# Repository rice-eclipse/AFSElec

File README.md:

This is the official GitHub Repo for Rice ECLIPSE AFS.

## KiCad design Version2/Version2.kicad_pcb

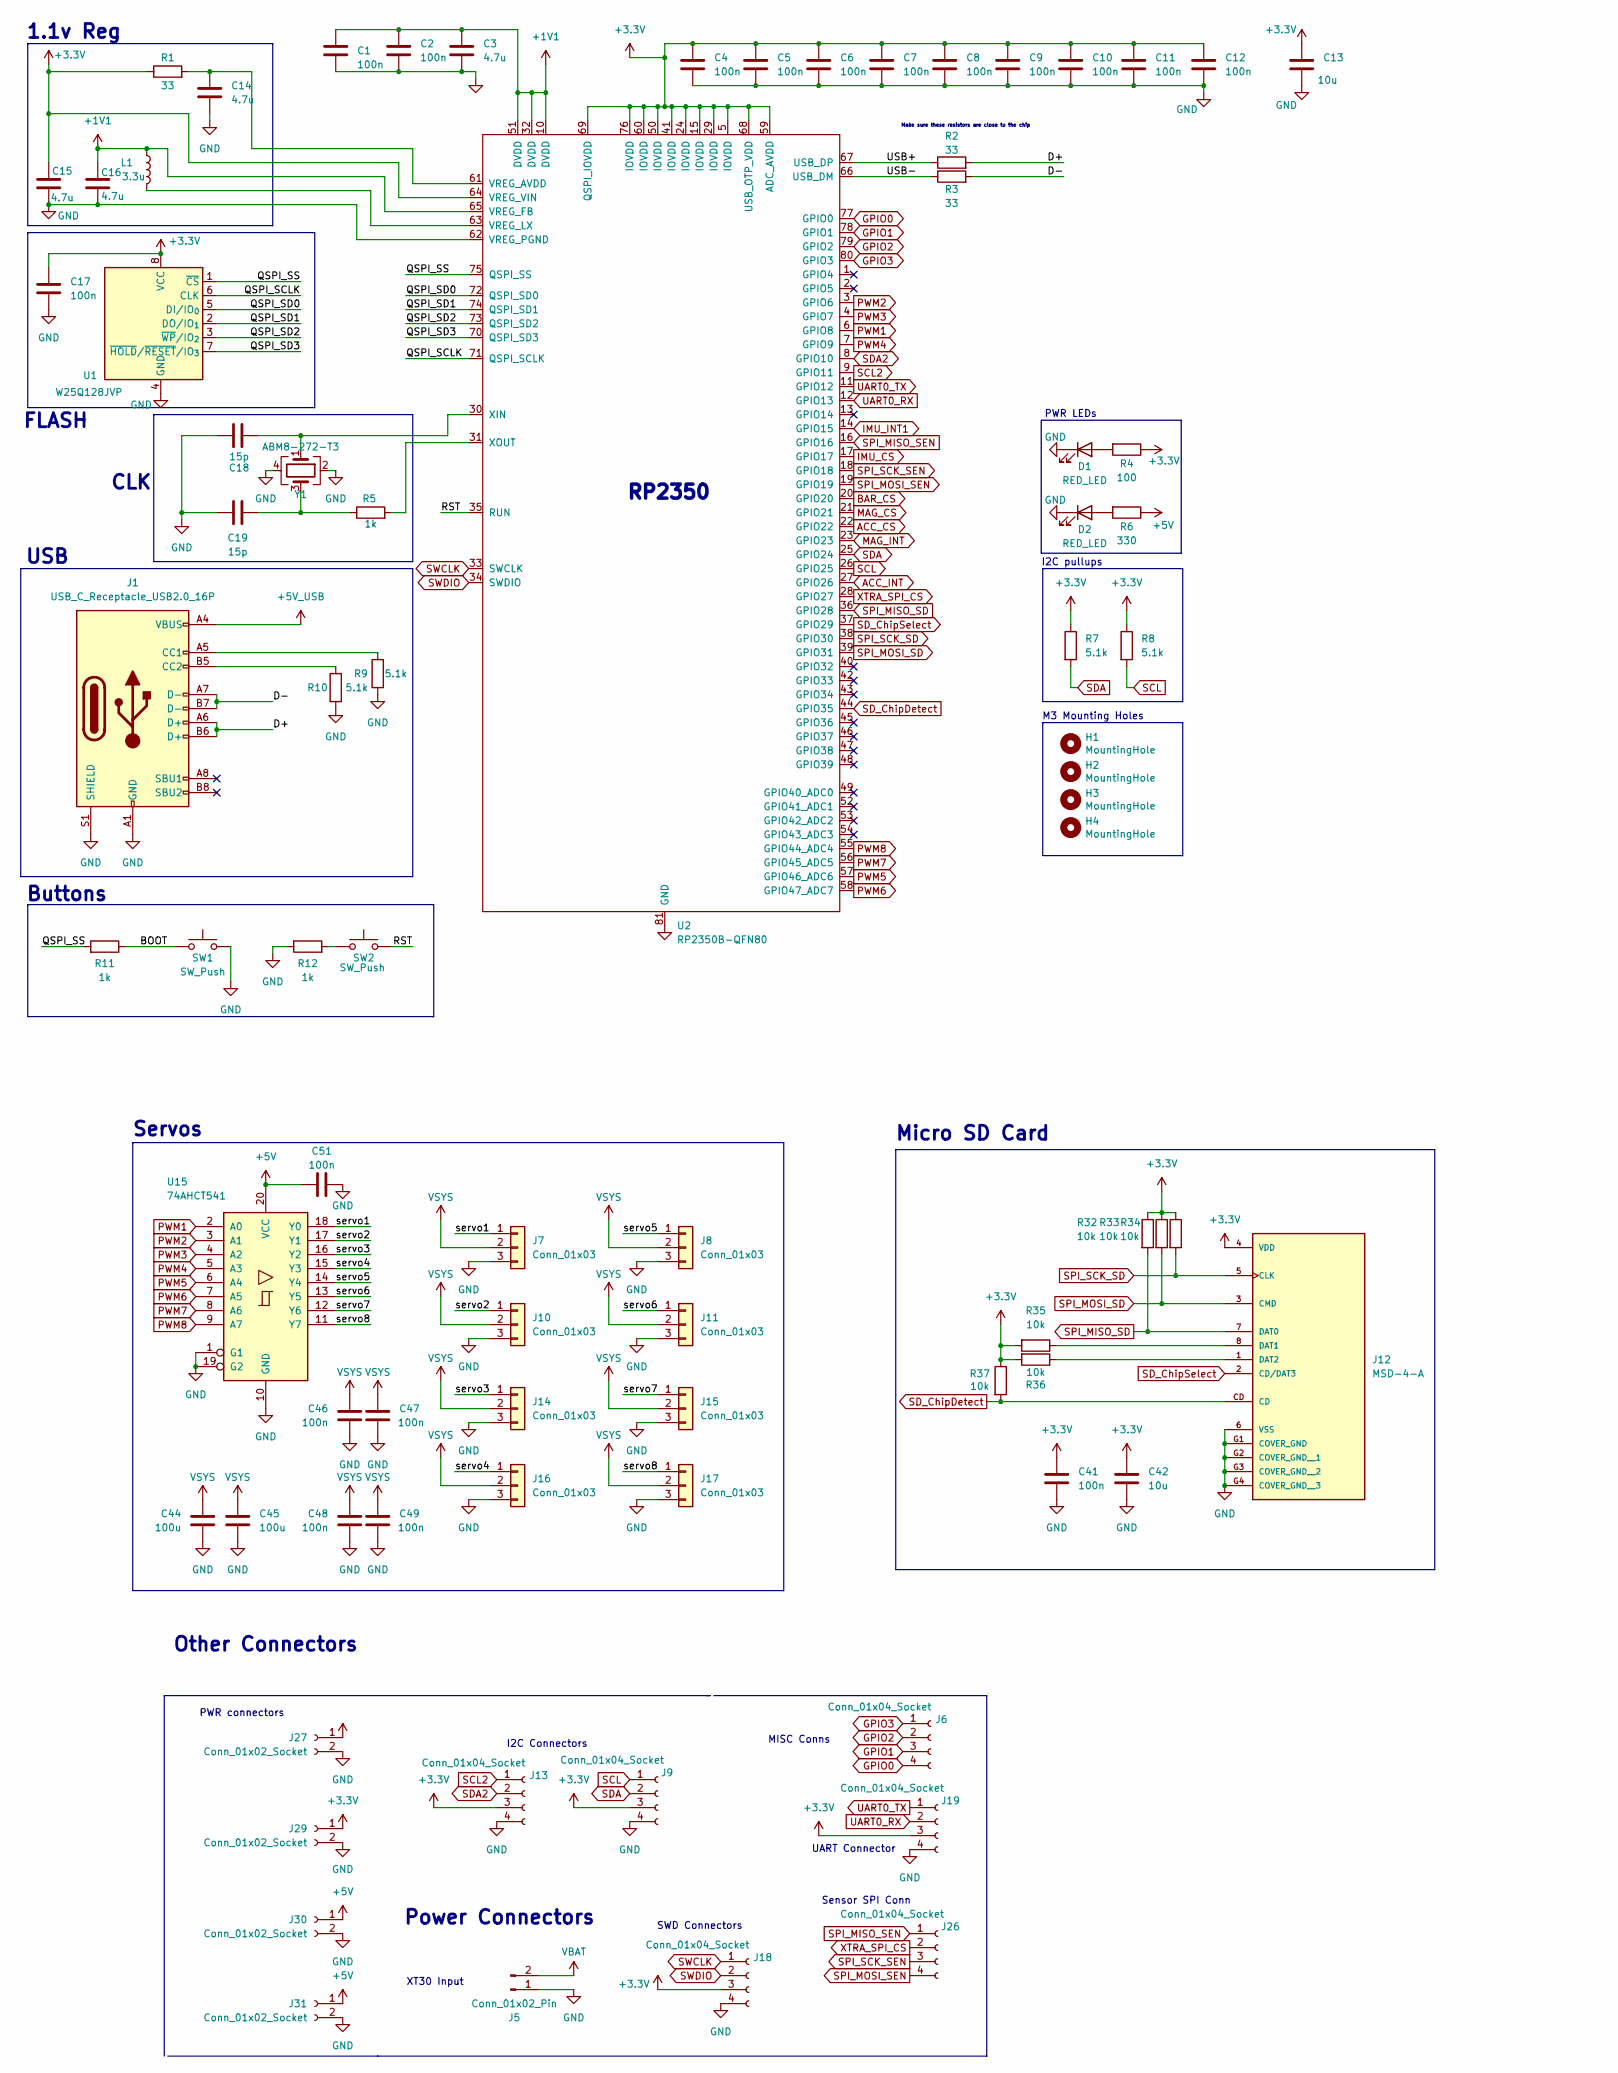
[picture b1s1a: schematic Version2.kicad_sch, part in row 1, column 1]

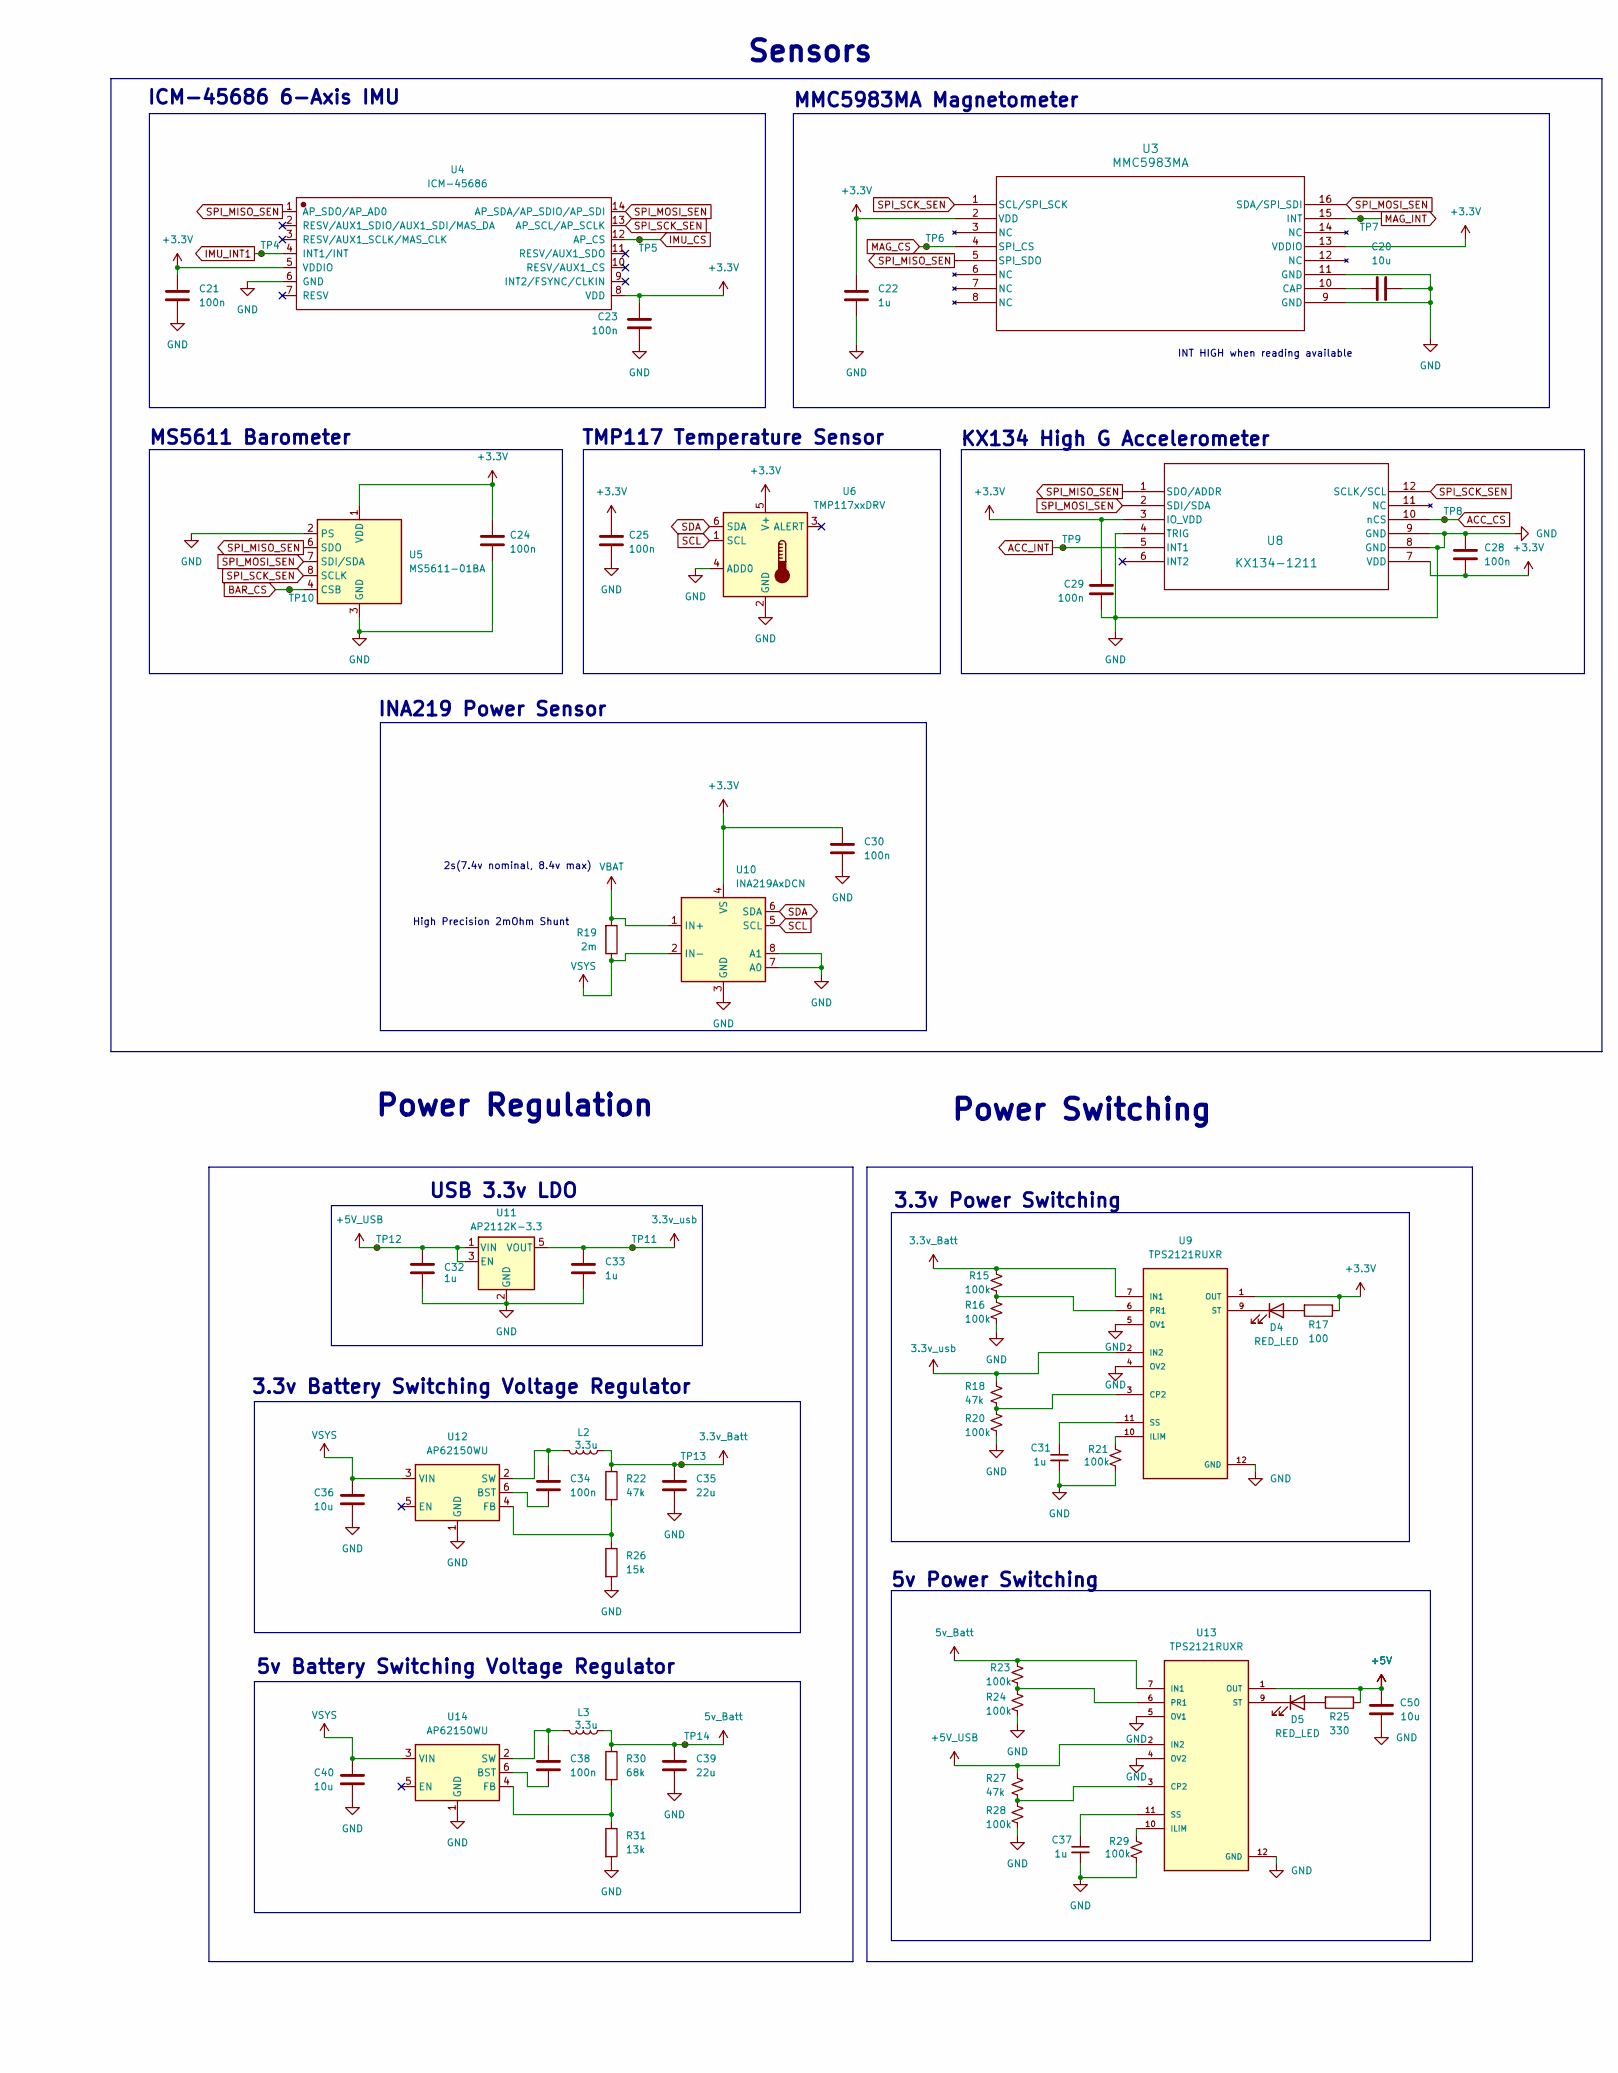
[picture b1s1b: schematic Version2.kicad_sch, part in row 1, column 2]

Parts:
C1, C2, C4, C5, C6, C7, C8, C9, C10, C11, C12, C17, C21, C23, C24, C25, C28, C29, C30, C34, C38, C41, C46, C47, C48, C49, C51: 100n; C_0603_1608Metric; LCSC Part Number C14663
C3, C14, C15, C16: 4.7u; C_0805_2012Metric; LCSC Part Number C1779
C13, C20, C42: 10u; C_0805_2012Metric; LCSC Part Number C15850
C18, C19: 15p; C_0603_1608Metric; LCSC Part Number C1644
C22, C31, C32, C33, C37: 1u; C_0805_2012Metric; LCSC Part Number C28323
C35, C39: 22u; C_0805_2012Metric; LCSC Part Number C45783
C36, C40, C50: 10u; C_0805_2012Metric; JLCPCB Part # C15850
C44, C45: 100u; C_Radial_D5.0mm_H11.0mm_P2.00mm
D1, D2, D4, D5: RED_LED; LED_0805_2012Metric; LCSC Part Number C84256
H1, H2, H3, H4: MountingHole; MountingHole_3.2mm_M3_ISO14580_Pad
J1: USB_C_Receptacle_USB2.0_16P; USB_C_Receptacle_HRO_TYPE-C-31-M-12
J5: Conn_01x02_Pin; AMASS_XT30PW-M_1x02_P2.50mm_Horizontal
J6, J9, J13, J18, J19, J26: Conn_01x04_Socket; JST_PH_B4B-PH-K_1x04_P2.00mm_Vertical
J7, J8, J10, J11, J14, J15, J16, J17: Conn_01x03; PinHeader_1x03_P2.54mm_Vertical
J12: MSD-4-A; CUI_MSD-4-A; PARTREV 1.0; LCSC Part Number C22367949
J27, J29, J30, J31: Conn_01x02_Socket; JST_PH_B2B-PH-K_1x02_P2.00mm_Vertical
L1, L2, L3: 3.3u; AOTA-B201610S3R3-101-T(L_0806_2016metric); LCSC Part Number C42411119
R1, R2, R3: 33; R_0603_1608Metric; LCSC Part Number C23140
R4, R17: 100; R_0603_1608Metric; LCSC Part Number C22775
R5, R11, R12: 1k; R_0603_1608Metric; LCSC Part Number C21190
R6, R25: 330; R_0603_1608Metric; LCSC Part Number C23138
R7, R8, R9, R10: 5.1k; R_0603_1608Metric; LCSC Part Number C23186
R15, R16, R20, R21, R23, R24, R28, R29: 100k; R_0603_1608Metric; LCSC Part Number C25803
R18, R22, R27: 47k; R_0603_1608Metric; LCSC Part Number C25819
R19: 2m; R_1206_3216Metric
R26: 15k; R_0603_1608Metric; LCSC Part Number C22809
R30: 68k; R_0603_1608Metric; LCSC Part Number C23231
R31: 13k; R_0603_1608Metric; LCSC Part Number C22797
R32, R33, R34, R35, R36, R37: 10k; R_0603_1608Metric; LCSC Part Number C25804
SW1, SW2: SW_Push; SW_Push_SPST_NO_Alps_SKRK; LCSC Part Number C115357
TP4, TP5, TP6, TP7, TP8, TP9, TP10, TP11, TP12, TP13, TP14: TestPoint_Small; TestPoint_Pad_1.0x1.0mm
U1: W25Q128JVP; WSON-8-1EP_6x5mm_P1.27mm_EP3.4x4mm; LCSC Part Number C190862
U2: RP2350B-QFN80; QFN-80-1EP_10x10mm_P0.4mm_EP3.4x3.4mm; LCSC Part Number C42415655
U3: MMC5983MA; LGA-16_3x3mm_P0.5mm; LCSC Part Number C404329
U4: ICM-45686; Bosch_LGA-14_3x2.5mm_P0.5mm; Manufacturer Part ICM-45686; LCSC C22459454
U5: MS5611-01BA; LGA-8_3x5mm_P1.25mm; LCSC Part Number C15639
U6: TMP117xxDRV; WSON-6-1EP_2x2mm_P0.65mm_EP1x1.6mm; LCSC Part Number C699536
U8: KX134-1211; LGA-12_2x2mm_P0.5mm; LCSC Part Number C2157908
U9, U13: TPS2121RUXR; Texas_VQFN-HR-12_2x2.5mm_P0.5mm; LCSC Part Number C485916
U10: INA219AxDCN; SOT-23-8; LCSC Part Number SOT-23-8
U11: AP2112K-3.3; SOT-23-5; LCSC Part Number C23380830
U12, U14: AP62150WU; TSOT-23-6; LCSC Part Number C3194237
U15: 74AHCT541; SSOP-20_4.4x6.5mm_P0.65mm; LCSC Part Number C2675635
Y1: ABM8-272-T3; Crystal_SMD_3225-4Pin_3.2x2.5mm; LCSC Part Number C20625731

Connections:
3.3v_Batt: C35.1, L2.1, R15.1, R22.1, TP13.1, U9.7 (IN1)
3.3v_usb: C33.1, R18.1, TP11.1, U9.2 (IN2), U11.5 (VOUT)
5v_Batt: C39.1, L3.1, R23.1, R30.1, TP14.1, U13.7 (IN1)
+1V1: C1.1, C2.1, C3.1, C16.1, L1.1, U2.10 (DVDD), U2.32 (DVDD), U2.51 (DVDD), U2.65 (VREG_FB)
+3.3V: C4.1, C5.1, C6.1, C7.1, C8.1, C9.1, C10.1, C11.1, C12.1, C13.1, C15.1, C17.1, C21.1, C22.2, C23.1, C24.1, C25.1, C28.2, C29.1, C30.1, C41.1, C42.1, J9.3, J12.4 (VDD), J13.3, J18.3, J19.3, J27.1, J29.1, R1.1, R4.1, R7.1, R8.1, R17.1, R32.1, R33.1, R34.1, R35.2, R36.2, R37.1, U1.8 (VCC), U2.5 (IOVDD), U2.15 (IOVDD), U2.24 (IOVDD), U2.29 (IOVDD), U2.41 (IOVDD), U2.50 (IOVDD), U2.59 (ADC_AVDD), U2.60 (IOVDD), U2.64 (VREG_VIN), U2.68 (USB_OTP_VDD), U2.69 (QSPI_IOVDD), U2.76 (IOVDD), U3.2 (VDD), U3.13 (VDDIO), U4.5 (VDDIO), U4.8 (VDD), U5.1 (VDD), U6.5 (V+), U8.3 (IO_VDD), U8.7 (VDD), U9.1 (OUT), U9.8 (OUT), U10.4 (VS)
+5V: C50.1, C51.1, J30.1, J31.1, R6.1, R25.1, U13.1 (OUT), U13.8 (OUT), U15.20 (VCC)
+5V_USB: C32.1, J1.A4 (VBUS), J1.A9 (VBUS), J1.B4 (VBUS), J1.B9 (VBUS), R27.1, TP12.1, U11.1 (VIN), U11.3 (EN), U13.2 (IN2)
/BOOT: R11.1, SW1.2
/D+: J1.A6 (D+), J1.B6 (D+), R2.2
/D-: J1.A7 (D-), J1.B7 (D-), R3.2
/QSPI_SCLK: U1.6 (CLK), U2.71 (QSPI_SCLK)
/QSPI_SD0: U1.5 (DI/IO_{0}), U2.72 (QSPI_SD0)
/QSPI_SD1: U1.2 (DO/IO_{1}), U2.74 (QSPI_SD1)
/QSPI_SD2: U1.3 (~WP/IO_{2}), U2.73 (QSPI_SD2)
/QSPI_SD3: U1.7 (~HOLD/~RESET/IO_{3}), U2.70 (QSPI_SD3)
/QSPI_SS: R11.2, U1.1 (~CS), U2.75 (QSPI_SS)
/RST: SW2.2, U2.35 (RUN)
/USB+: R2.1, U2.67 (USB_DP)
/USB-: R3.1, U2.66 (USB_DM)
/servo1: J7.1, U15.18 (Y0)
/servo2: J10.1, U15.17 (Y1)
/servo3: J14.1, U15.16 (Y2)
/servo4: J16.1, U15.15 (Y3)
/servo5: J8.1, U15.14 (Y4)
/servo6: J11.1, U15.13 (Y5)
/servo7: J15.1, U15.12 (Y6)
/servo8: J17.1, U15.11 (Y7)
ACC_CS: TP8.1, U2.22 (GPIO22), U8.10 (nCS)
ACC_INT: TP9.1, U2.27 (GPIO26), U8.5 (INT1)
BAR_CS: TP10.1, U2.20 (GPIO20), U5.4 (CSB), U5.5 (CSB)
GND: C1.2, C2.2, C3.2, C4.2, C5.2, C6.2, C7.2, C8.2, C9.2, C10.2, C11.2, C12.2, C13.2, C14.2, C15.2, C16.2, C17.2, C18.1, C19.1, C20.2, C21.2, C22.1, C23.2, C24.2, C25.2, C28.1, C29.2, C30.2, C31.2, C32.2, C33.2, C35.2, C36.2, C37.2, C39.2, C40.2, C41.2, C42.2, C44.2, C45.2, C46.2, C47.2, C48.2, C49.2, C50.2, C51.2, D1.1 (K), D2.1 (K), J1.A1 (GND), J1.A12 (GND), J1.B1 (GND), J1.B12 (GND), J1.S1 (SHIELD), J5.1, J7.3, J8.3, J9.4, J10.3, J11.3, J12.6 (VSS), J12.G1 (COVER_GND), J12.G2 (COVER_GND__1), J12.G3 (COVER_GND__2), J12.G4 (COVER_GND__3), J13.4, J14.3, J15.3, J16.3, J17.3, J18.4, J19.4, J27.2, J29.2, J30.2, J31.2, R9.1, R10.1, R12.1, R16.2, R20.2, R21.2, R24.2, R26.2, R28.2, R29.2, R31.2, SW1.1, U1.4 (GND), U2.62 (VREG_PGND), U2.81 (GND), U3.9 (GND), U3.11 (GND), U4.6 (GND), U5.2 (PS), U5.3 (GND), U6.2 (GND), U6.4 (ADD0), U8.4 (TRIG), U8.8 (GND), U8.9 (GND), U9.4 (OV2), U9.5 (OV1), U9.12 (GND), U10.3 (GND), U10.7 (A0), U10.8 (A1), U11.2 (GND), U12.1 (GND), U13.4 (OV2), U13.5 (OV1), U13.12 (GND), U14.1 (GND), U15.1 (G1), U15.10 (GND), U15.19 (G2), Y1.2, Y1.4
GPIO0: J6.4, U2.77 (GPIO0)
GPIO1: J6.3, U2.78 (GPIO1)
GPIO2: J6.2, U2.79 (GPIO2)
GPIO3: J6.1, U2.80 (GPIO3)
IMU_CS: TP5.1, U2.17 (GPIO17), U4.12 (AP_CS)
IMU_INT1: TP4.1, U2.14 (GPIO15), U4.4 (INT1/INT)
MAG_CS: TP6.1, U2.21 (GPIO21), U3.4 (SPI_CS)
MAG_INT: TP7.1, U2.23 (GPIO23), U3.15 (INT)
unnamed: C19.2, R5.1, Y1.3
unnamed: D1.2 (A), R4.2
unnamed: D2.2 (A), R6.2
unnamed: D4.2 (A), R17.2
unnamed: D4.1 (K), U9.9 (ST)
unnamed: D5.2 (A), R25.2
unnamed: D5.1 (K), U13.9 (ST)
unnamed: J1.A5 (CC1), R9.2
unnamed: J1.B5 (CC2), R10.2
unnamed: J12.8 (DAT1), R35.1
unnamed: J12.1 (DAT2), R36.1
unnamed: R12.2, SW2.1
unnamed: C14.1, R1.2, U2.61 (VREG_AVDD)
unnamed: L1.2, U2.63 (VREG_LX)
unnamed: C18.2, U2.30 (XIN), Y1.1
unnamed: R5.2, U2.31 (XOUT)
unnamed: C20.1, U3.10 (CAP)
unnamed: R18.2, R20.1, U9.3 (CP2)
unnamed: R21.1, U9.10 (ILIM)
unnamed: R15.2, R16.1, U9.6 (PR1)
unnamed: C31.1, U9.11 (SS)
unnamed: C34.2, U12.6 (BST)
unnamed: R22.2, R26.1, U12.4 (FB)
unnamed: C34.1, L2.2, U12.2 (SW)
unnamed: R27.2, R28.1, U13.3 (CP2)
unnamed: R29.1, U13.10 (ILIM)
unnamed: R23.2, R24.1, U13.6 (PR1)
unnamed: C37.1, U13.11 (SS)
unnamed: C38.2, U14.6 (BST)
unnamed: R30.2, R31.1, U14.4 (FB)
unnamed: C38.1, L3.2, U14.2 (SW)
PWM1: U2.6 (GPIO8), U15.2 (A0)
PWM2: U2.3 (GPIO6), U15.3 (A1)
PWM3: U2.4 (GPIO7), U15.4 (A2)
PWM4: U2.7 (GPIO9), U15.5 (A3)
PWM5: U2.57 (GPIO46_ADC6), U15.6 (A4)
PWM6: U2.58 (GPIO47_ADC7), U15.7 (A5)
PWM7: U2.56 (GPIO45_ADC5), U15.8 (A6)
PWM8: U2.55 (GPIO44_ADC4), U15.9 (A7)
SCL: J9.1, R8.2, U2.26 (GPIO25), U6.1 (SCL), U10.5 (SCL)
SCL2: J13.1, U2.9 (GPIO11)
SDA: J9.2, R7.2, U2.25 (GPIO24), U6.6 (SDA), U10.6 (SDA)
SDA2: J13.2, U2.8 (GPIO10)
SD_ChipDetect: J12.CD, R37.2, U2.44 (GPIO35)
SD_ChipSelect: J12.2 (CD/DAT3), U2.37 (GPIO29)
SPI_MISO_SD: J12.7 (DAT0), R32.2, U2.36 (GPIO28)
SPI_MISO_SEN: J26.1, U2.16 (GPIO16), U3.5 (SPI_SDO), U4.1 (AP_SDO/AP_AD0), U5.6 (SDO), U8.1 (SDO/ADDR)
SPI_MOSI_SD: J12.3 (CMD), R33.2, U2.39 (GPIO31)
SPI_MOSI_SEN: J26.4, U2.19 (GPIO19), U3.16 (SDA/SPI_SDI), U4.14 (AP_SDA/AP_SDIO/AP_SDI), U5.7 (SDI/SDA), U8.2 (SDI/SDA)
SPI_SCK_SD: J12.5 (CLK), R34.2, U2.38 (GPIO30)
SPI_SCK_SEN: J26.3, U2.18 (GPIO18), U3.1 (SCL/SPI_SCK), U4.13 (AP_SCL/AP_SCLK), U5.8 (SCLK), U8.12 (SCLK/SCL)
SWCLK: J18.1, U2.33 (SWCLK)
SWDIO: J18.2, U2.34 (SWDIO)
UART0_RX: J19.2, U2.12 (GPIO13)
UART0_TX: J19.1, U2.11 (GPIO12)
VBAT: J5.2, R19.2, U10.1 (IN+)
VSYS: C36.1, C40.1, C44.1, C45.1, C46.1, C47.1, C48.1, C49.1, J7.2, J8.2, J10.2, J11.2, J14.2, J15.2, J16.2, J17.2, R19.1, U10.2 (IN-), U12.3 (VIN), U14.3 (VIN)
XTRA_SPI_CS: J26.2, U2.28 (GPIO27)

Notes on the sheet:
INT HIGH when reading available
USB 3.3v LDO
I2C Connectors
TMP117 Temperature Sensor
RP2350
Power Connectors
Buttons
5v Power Switching
3.3v Power Switching
Power Regulation
INA219 Power Sensor
Sensor SPI Conn
KX134 High G Accelerometer
ICM-45686 6-Axis IMU
Other Connectors
3.3v Battery Switching Voltage Regulator
2s(7.4v nominal, 8.4v max)
5v Battery Switching Voltage Regulator
SWD Connectors
CLK
Sensors
XT30 Input
I2C pullups
Make sure these resistors are close to the chip
M3 Mounting Holes
FLASH
MS5611 Barometer
High Precision 2mOhm Shunt
MMC5983MA Magnetometer
PWR LEDs
Power Switching
UART Connector
Servos
1.1v Reg
Micro SD Card
USB
PWR connectors
MISC Conns

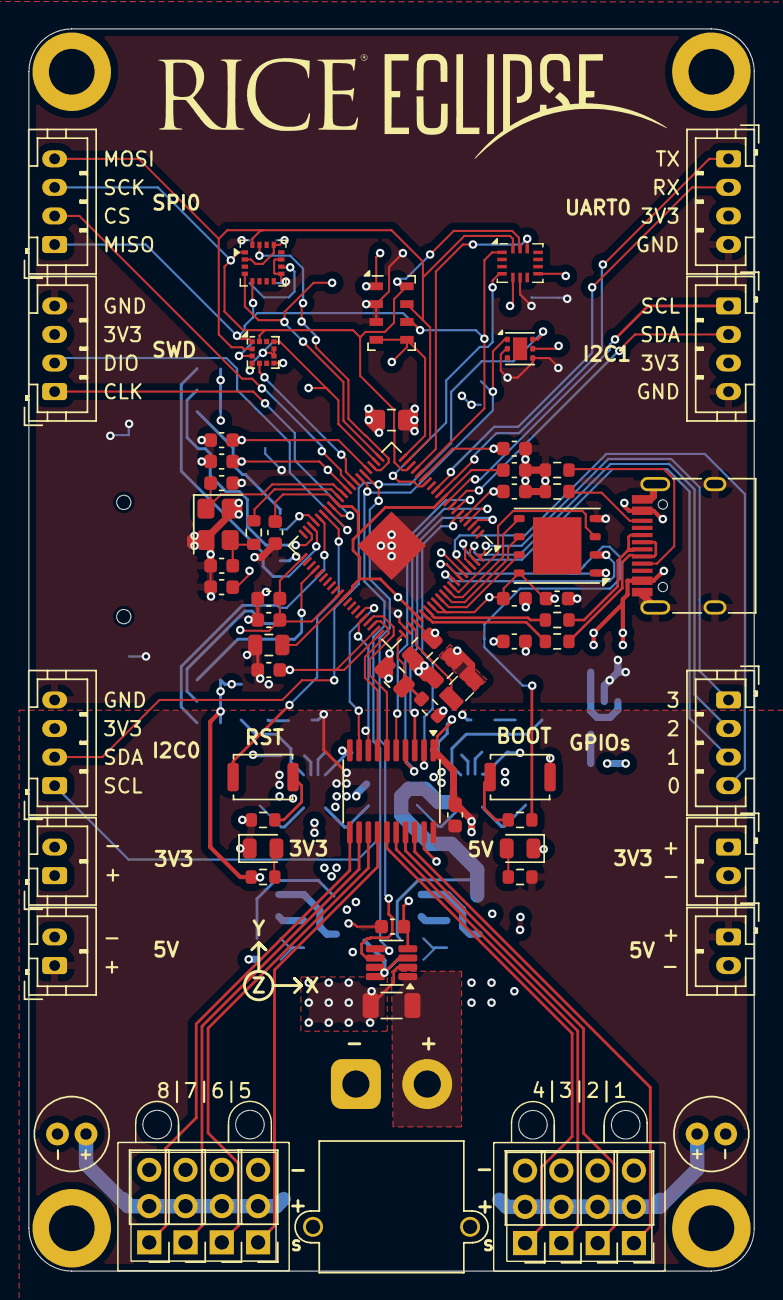
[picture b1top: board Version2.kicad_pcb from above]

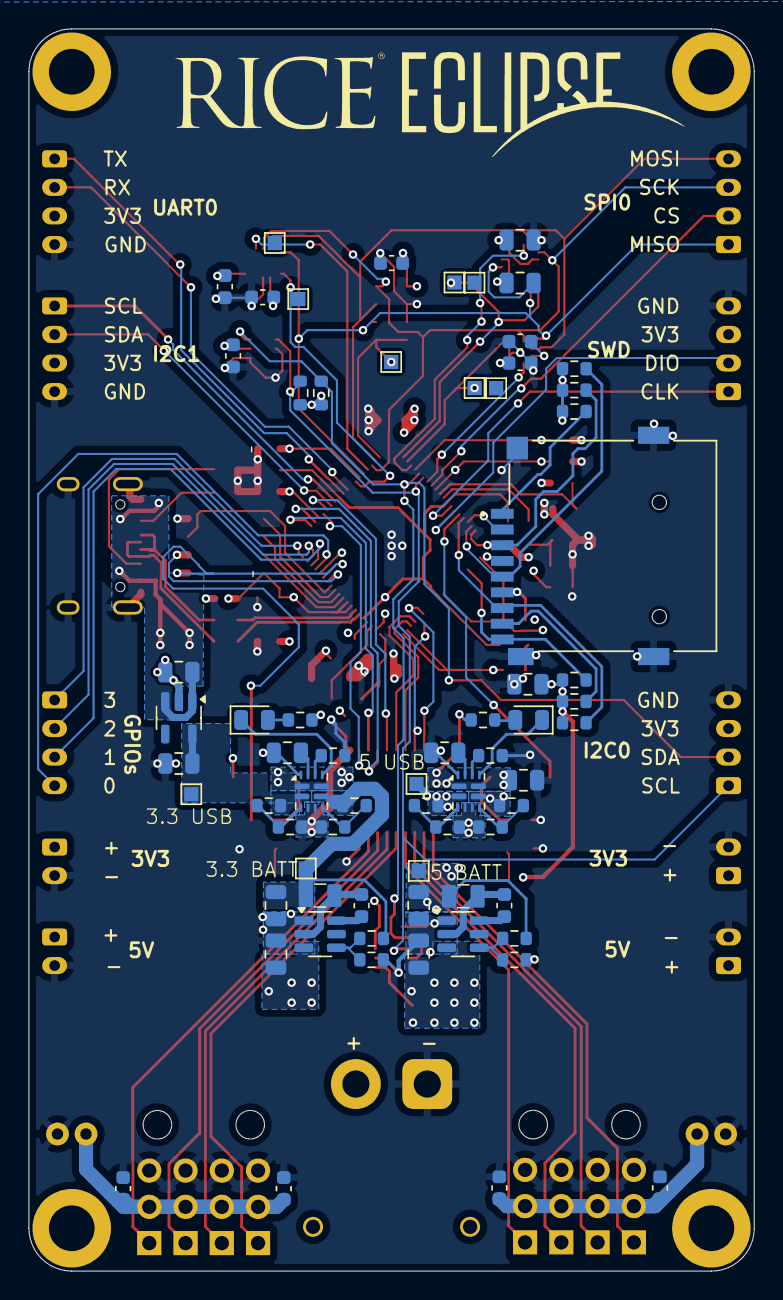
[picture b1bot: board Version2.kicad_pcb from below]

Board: 4 copper layers, 50.8 x 87.0 mm, 146 parts (69 on the bottom side), 97 nets.

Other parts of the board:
G1, G2: 3x4PinHeaderCase90deg
G3: orientationIndicator

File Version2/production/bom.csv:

Designator,Footprint,Quantity,Value,LCSC Part #
"C1, C10, C11, C12, C17, C2, C21, C23, C24, C25, C28, C29, C30, C34, C38, C4, C41, C5, C51, C6, C7, C8, C9",0603,23,100n,C1525
"C13, C20, C36, C40, C42, C50",0805,6,10u,C15850
"C14, C15, C16, C3",0805,4,4.7u,C23733
"C18, C19",0603,2,15p,C1548
"C22, C31, C37",0805,3,1u,C28323
"C32, C33",0805,2,1u,C15850
"C35, C39",0805,2,22u,C45783
"C44, C45",C_Radial_D5.0mm_H11.0mm_P2.00mm,2,100u,C15850
"C46, C47, C48, C49",0603,4,100n,C15850
"D1, D2, D4, D5",0805,4,RED_LED,C84256
"G1, G2",3x4PinHeaderCase90deg,2,3x4PinHeaderCase90deg,
G3,orientationIndicator,1,orientationIndicator,
"H1, H2, H3, H4",MountingHole_3.2mm_M3_ISO14580_Pad,4,MountingHole,
J1,USB_C_Receptacle_HRO_TYPE-C-31-M-12,1,USB_C_Receptacle_USB2.0_16P,
"J10, J11, J14, J15, J16, J17, J7, J8",PinHeader_1x03_P2.54mm_Vertical,8,Conn_01x03,
J12,CUI_MSD-4-A,1,MSD-4-A,
"J13, J18, J19, J26, J6, J9",JST_PH_B4B-PH-K_1x04_P2.00mm_Vertical,6,Conn_01x04_Socket,
"J27, J29, J30, J31",JST_PH_B2B-PH-K_1x02_P2.00mm_Vertical,4,Conn_01x02_Socket,
J5,AMASS_XT30PW-M_1x02_P2.50mm_Horizontal,1,Conn_01x02_Pin,
"L1, L2, L3",AOTA-B201610S3R3-101-T(L_0806_2016metric),3,3.3u,
R1,0603,1,33,C25105
"R10, R9",0603,2,5.1k,C25105
"R11, R12, R5",0603,3,1k,C11702
"R15, R23",0603,2,100k,C25792
"R16, R20, R21, R24, R28, R29",0603,6,100k,C25741
"R17, R4",0603,2,100,C25076
"R18, R27",0603,2,47k,C25741
R19,1206,1,2m,
"R2, R3",0603,2,33,C25092
R22,0603,1,47k,C25792
"R25, R6",0603,2,330,C25076
R26,0603,1,15k,C25756
R30,0603,1,68k,C25792
R31,0603,1,13k,C25756
"R32, R33, R34, R35, R36, R37",0603,6,10k,C25744
"R7, R8",0603,2,5.1k,C25900
"SW1, SW2",SW_Push_SPST_NO_Alps_SKRK,2,SW_Push,
"TP10, TP11, TP12, TP13, TP14, TP4, TP5, TP6, TP7, TP8, TP9",TestPoint_Pad_1.0x1.0mm,11,TestPoint_Small,
U1,WSON-8-1EP_6x5mm_P1.27mm_EP3.4x4mm,1,W25Q128JVS,C97521
U10,SOT-23-8,1,INA219AxDCN,
U11,SOT-23-5,1,AP2112K-3.3,
"U12, U14",TSOT-23-6,2,AP62150WU,C3194237
"U13, U9",Texas_VQFN-HR-12_2x2.5mm_P0.5mm,2,TPS2121RUXR,C485916
U15,SSOP-20_4.4x6.5mm_P0.65mm,1,74AHCT541,
U2,QFN-80-1EP_10x10mm_P0.4mm_EP3.4x3.4mm,1,RP2350B-QFN80,
U3,LGA-16_3x3mm_P0.5mm,1,MMC5983MA,C404329
U4,Bosch_LGA-14_3x2.5mm_P0.5mm,1,ICM-45686,C22459454
U5,LGA-8_3x5mm_P1.25mm,1,MS5611-01BA,C15639
U6,WSON-6-1EP_2x2mm_P0.65mm_EP1x1.6mm,1,TMP117xxDRV,
U8,LGA-12_2x2mm_P0.5mm,1,KX134-1211,C2157908
Y1,Crystal_SMD_3225-4Pin_3.2x2.5mm,1,ABM8-272-T3,C20625731
